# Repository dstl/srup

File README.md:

# SRUP

## Secure Remote Update Protocol
The Secure Remote Update Protocol (SRUP) is a secure & confirmable command-and-control (C2) protocol for the Internet of Things (IoT), based on MQTT.

SRUP is designed to provide an easy way to communicate details of a required software update to an IoT device – but it's not limited just software updates; the protocol can be extended to support any type of C2 message.

**This software is the output of PhD research; and whilst appropriate due diligence has been carried out in terms of quality assurance – this software is not a formal Dstl output; please see the terms of release as outlined in the MIT Licence within this repository..**

Further details of the protocol may be found in the papers:
* SRUP: The Secure Remote Update Protocol (published at the IEEE World Forum on the Internet of Things, 12th December 2016) - http://ieeexplore.ieee.org/document/7845397/

* Extensions and Enhancements to "the Secure Remote Update Protocol" (published in Volume 9, issue 4 of the Journal 'Future Internet') - http://www.mdpi.com/1999-5903/9/4/59

* pySRUP – Simplifying Secure Communications for Command & Control in the Internet of Things (published at the 5th IEEE World Forum on the Internet of Things, 15-18 April 2019) - https://ieeexplore.ieee.org/document/8767205

* Enabling the Secure Use of Dynamic Identity for the Internet of Things—Using the Secure Remote Update Protocol (published in Volume 12, issue 8 of the Journal 'Future Internet') - https://www.mdpi.com/1999-5903/12/8/138

* Enabling Secure Guest Access for Command-and-Control of Internet of Things Devices (published in Volume 2, issue 2 of the Journal 'IoT') -  https://www.mdpi.com/2624-831X/2/2/13

* An Assessment of the Performance of the Secure Remote Update Protocol in Simulated Real-World Conditions (published in Volume 2, issue 4 of the Journal 'IoT') -  https://www.mdpi.com/2624-831X/2/4/28

* Secure Messaging, Key Management & Device Identity for the IoT (presentation to IoT Security Foundation Conference, November 2019) – https://youtu.be/vdjY617WvHo 

* The Secure Remote Update Protocol in Action – Video demonstration – https://youtu.be/F0_qlqh0Oiw

The latest release of the source code can be accessed via

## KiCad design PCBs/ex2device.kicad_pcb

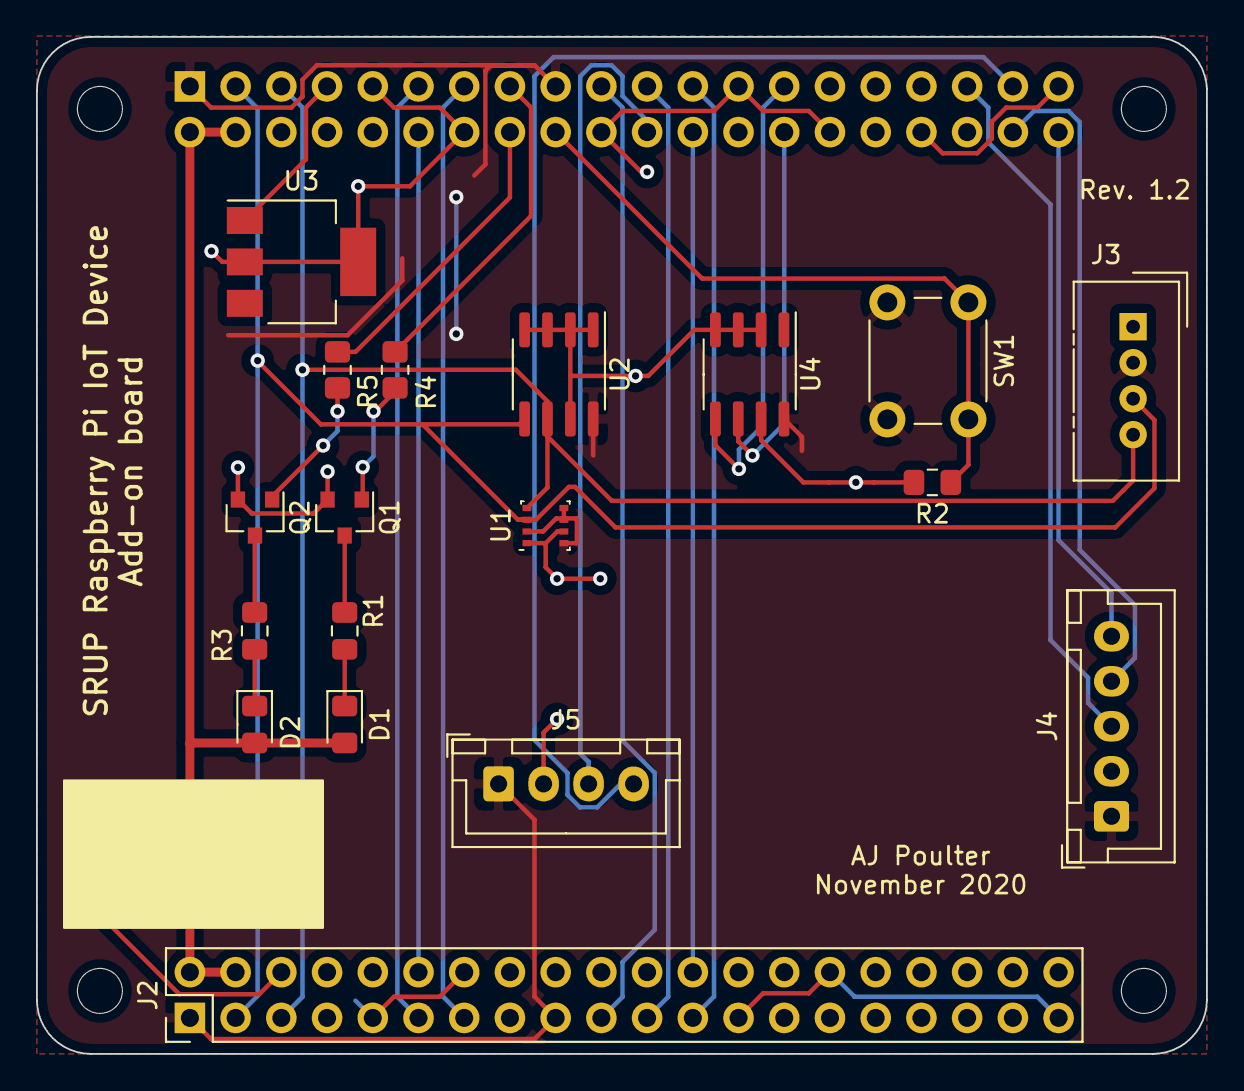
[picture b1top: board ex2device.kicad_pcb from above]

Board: 2 copper layers, 65.0 x 56.5 mm, 23 parts (1 on the bottom side), 29 nets.

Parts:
D1: LED (Red); LED_0805_2012Metric_Pad1.15x1.40mm_HandSolder
D2: LED (Green); LED_0805_2012Metric_Pad1.15x1.40mm_HandSolder
H1, H2, H3, H4: MountingHole; MountingHole_2.5mm
J1, J2: Raspberry_Pi_2_3; PinHeader_2x20_P2.54mm_Vertical
J3: Conn_01x04_Female; NS-Tech_Grove_1x04_P2mm_Vertical
J4: Conn_01x05_Male; JST_XH_B5B-XH-A_1x05_P2.50mm_Vertical
J5: Conn_01x04_Male; JST_XH_B4B-XH-A_1x04_P2.50mm_Vertical
Q1, Q2: BC846 NPN; SOT-23
R1, R3: 470R; R_0805_2012Metric_Pad1.15x1.40mm_HandSolder
R2: 10K; R_0805_2012Metric_Pad1.15x1.40mm_HandSolder
R4, R5: 1K; R_0805_2012Metric_Pad1.20x1.40mm_HandSolder
SW1: SW_Push; SW_PUSH_6mm
U1: BME280; Bosch_LGA-8_2.5x2.5mm_P0.65mm_ClockwisePinNumbering
U2: 24LC256; SOIC-8_3.9x4.9mm_P1.27mm
U3: DS2401Z; SOT-223
U4: AT24CS04-SSHM; SOIC-8_3.9x4.9mm_P1.27mm

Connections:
+3V3: J1.1, J1.17, J2.1, J2.17, J3.2, J4.1, J5.1, SW1.2, U1.2, U1.5, U1.6, U1.8, U2.8, U4.8
+5V: D1.2, D2.2, J1.2, J1.4, J2.2, J2.4
GND: J1.6, J1.9, J1.14, J1.20, J1.25, J1.30, J1.34, J1.39, J2.6, J2.9, J2.14, J2.20, J2.25, J2.30, J2.34, J2.39, J3.1, J4.2, J5.2, Q1.2, Q2.2, R2.1, U1.1, U1.7, U2.1, U2.2, U2.3, U2.4, U2.7, U3.2, U3.4, U4.2, U4.3, U4.4, U4.7
GPIO19: J1.35, J4.3
GPIO20: J1.38, J4.4
GPIO21: J1.40, J4.5
GPIO24: J1.18, R2.2, SW1.1
GPIO25: J1.22, J5.3
GPIO26: J1.37, J5.4
ID_SC: J1.28, U4.6
ID_SD: J1.27, U4.5
KEYIRQ: J1.13, J2.13
MISO: J1.21, J2.21
MOSI: J1.19, J2.19
unnamed: D1.1, R1.2
unnamed: D2.1, R3.2
unnamed: J1.15, R4.2
unnamed: J1.16, R5.2
unnamed: Q1.1, R4.1
unnamed: Q1.3, R1.1
unnamed: Q2.1, R5.1
unnamed: Q2.3, R3.1
PENIRQ: J1.11, J2.11
PWM: J1.12, J2.12
SCK: J1.23, J2.23
SCL1: J1.5, J2.5, J3.4, U1.4, U2.6
SDA1: J1.3, J2.3, J3.3, U1.3, U2.5
SPI-CS0: J1.24, J2.24
W1: J1.7, U3.1

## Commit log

2016-12-09 Initial Release
2016-12-09 Add LICENCE.txt
2016-12-09 Add notes.md
2017-02-21 Add URL for paper on IEEE Xplore.
2017-04-10 Add Sequence ID to messages - to protect against replay attacks
2017-09-29 Revert "Add Sequence ID to messages" - move to dev branch
    This reverts commit 831bb20ed2cb8528d747f13975954730b8fc09f9.
    Changes will be moved to a new Development branch: to ensure we retain a stable version.
2017-09-29 Create Development branch - add new message types & protection
    Change data types to use only fixed size datatypes, add Action & Data messages, add Sequence ID; remove client & server implementations (for now).
2017-09-29 Update README.md
    Add explanation of Development branch vs. Master.
2017-09-29 Update README.md
    Fix typo
2018-01-28 pySRUP Library Release
    Removes old demonstration application, creates pySRUP Python Library & demonstration application
2018-01-28 Add KeyExchange Server code
2018-01-30 Add dedicated build file for Raspberry Pi: CMakeLists.rpi.txt
2018-01-30 Update build.md
    Fix typo
2018-10-26 Update README.md
    Add DOI banner
2019-02-22 Update README.md
    Add DOI for release.
2019-03-19 Import version 2.0 from private development branch
2019-08-20 Update README.md
    Add WFIoT 2019 paper
2019-10-31 Update README.md
    Add emphasis to the disclaimer...
2019-11-21 Merge with private development branch for version 3.0 release.
    Merge with private development branch for version 3.0 release. This release adds the WebC2 functionality and user-moderated join functionality. It also provides example implementations of devices usi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
2021-05-11 Update README.md
    Add new papers
2021-05-11 Update README.md
    Fix broken image
2021-06-15 Add containerized backend & PCB design.
2021-06-15 Update KeyEx & KeyGen tools
    Add new KeyEx
    Add KeyGen tool
2021-09-27 Added links to new papers & videos to README.md
    Added links to new papers & videos to README.md
2021-09-27 Fix typo…
